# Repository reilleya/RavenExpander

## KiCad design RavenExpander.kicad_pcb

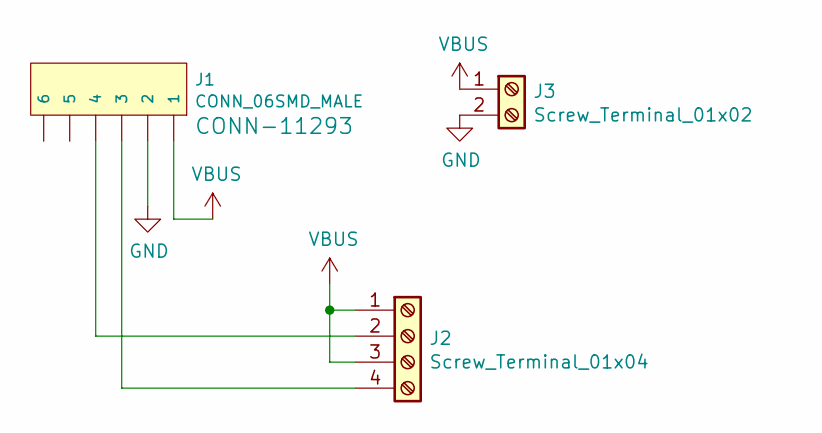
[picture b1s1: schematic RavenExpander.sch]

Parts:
J1: CONN_06SMD_MALE; PinHeader_1x06_P2.54mm_Vertical
J2: Screw_Terminal_01x04; SCREWTERMINAL-3.5MM-4
J3: Screw_Terminal_01x02; SCREWTERMINAL-3.5MM-2

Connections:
GND: J1.2, J3.2
unnamed: J1.3, J2.4
unnamed: J1.4, J2.2
VBUS: J1.1, J2.1, J2.3, J3.1

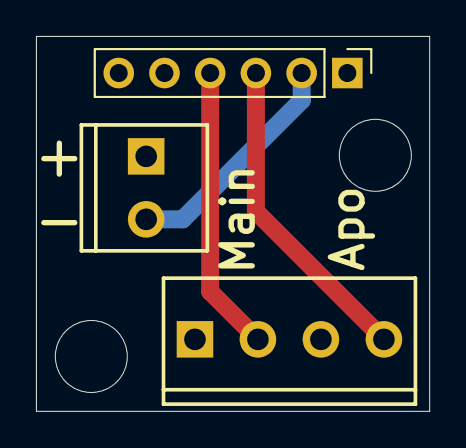
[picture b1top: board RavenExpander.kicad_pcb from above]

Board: 2 copper layers, 21.8 x 20.8 mm, 3 parts (0 on the bottom side), 4 nets.

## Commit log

2021-06-09 Add silkscreen
